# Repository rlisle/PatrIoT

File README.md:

# Patriot
Patriot is an open source, hobby IoT project using 
Particle.io Photon 2 devices, and optionally Siri, HomeKit, MQTT, and/or iOS apps.

It is intended to help other hobbyists quickly create Internet-of-Things
projects that can be controlled using Voice (Siri) and iOS devices
without having to recreate new HomeKit programming or iOS apps.

This project consists of published particle.io Photon 2
libraries (IoTlib and plugins).

Note that previously a published Alexa Smart Home skill (Patriot) was used.
The use of Alexa has been replaced with Siri and HomeKit. 
I apologize to those that want Alexa support, but it was getting to be too much work for me to support both iOS and Alexa by myself in my spare time.

The HomeKit "Home" app can be used with your old iPhones
to provide a touch display control panel.

Your Photon 2 based IoT projects can be created using any of the 
standard particle.io development tools (Web IDE,
Particle IDE, or Particle CLI).

The main objective is to allow the creation of networks of IoT
devices that can communicate with each other, and is:
1. Easily extensible: new devices can be added without having to modify existing devices.
2. Super simple to program
3. Reuses existing code, including the HomeKit apps, iOS apps, and Photon library code.

Refer to the older article [Alexa Controlled Photon Project without Alexa Coding](https://www.hackster.io/patriot-iot/alexa-controlled-photon-project-without-alexa-coding-f47d84)
on Hackster.io or my blog at lisles.net for some historical information.

## Devices
Particle.io Photon 2's are used due to their ease of use and great
support. I had originally created my own low cost printed circuit boards (PCBs), but since then ControlEverything (NCD.io) has released a series of Photon based boards that make it even easier to use.

These have wireless built-in, and can be programmed
over-the-air (OTA) so all they need is power to get started.

I've provided a set of source code files and instructions
that can be used to simplify
programming IoT devices using Particle's $19 Photon 2.

I've still publish the Eagle files and instructions for creating
general purpose IoT printed circuit boards.
PCBs can be ordered from China for about $1.50 each.
However, I've found that purchasing boards from NCD.io is quicker and the boards are much higher quality. The prices are very reasonable. For example, a simple Photon board with a power supply that works directly with my RV's 12v power and has screw terminals for connecting to the Photon's pins is only $15.

## Homebridge
HomeKit support is provided by Homebridge and the MQTTThingy plugin.

This allows Siri to control Patriot devices using your iPhone, Homepod, or Apple TV.

## Release History
Refer to the (Releases page)[https://github.com/rlisle/Patriot/releases]
for release history.

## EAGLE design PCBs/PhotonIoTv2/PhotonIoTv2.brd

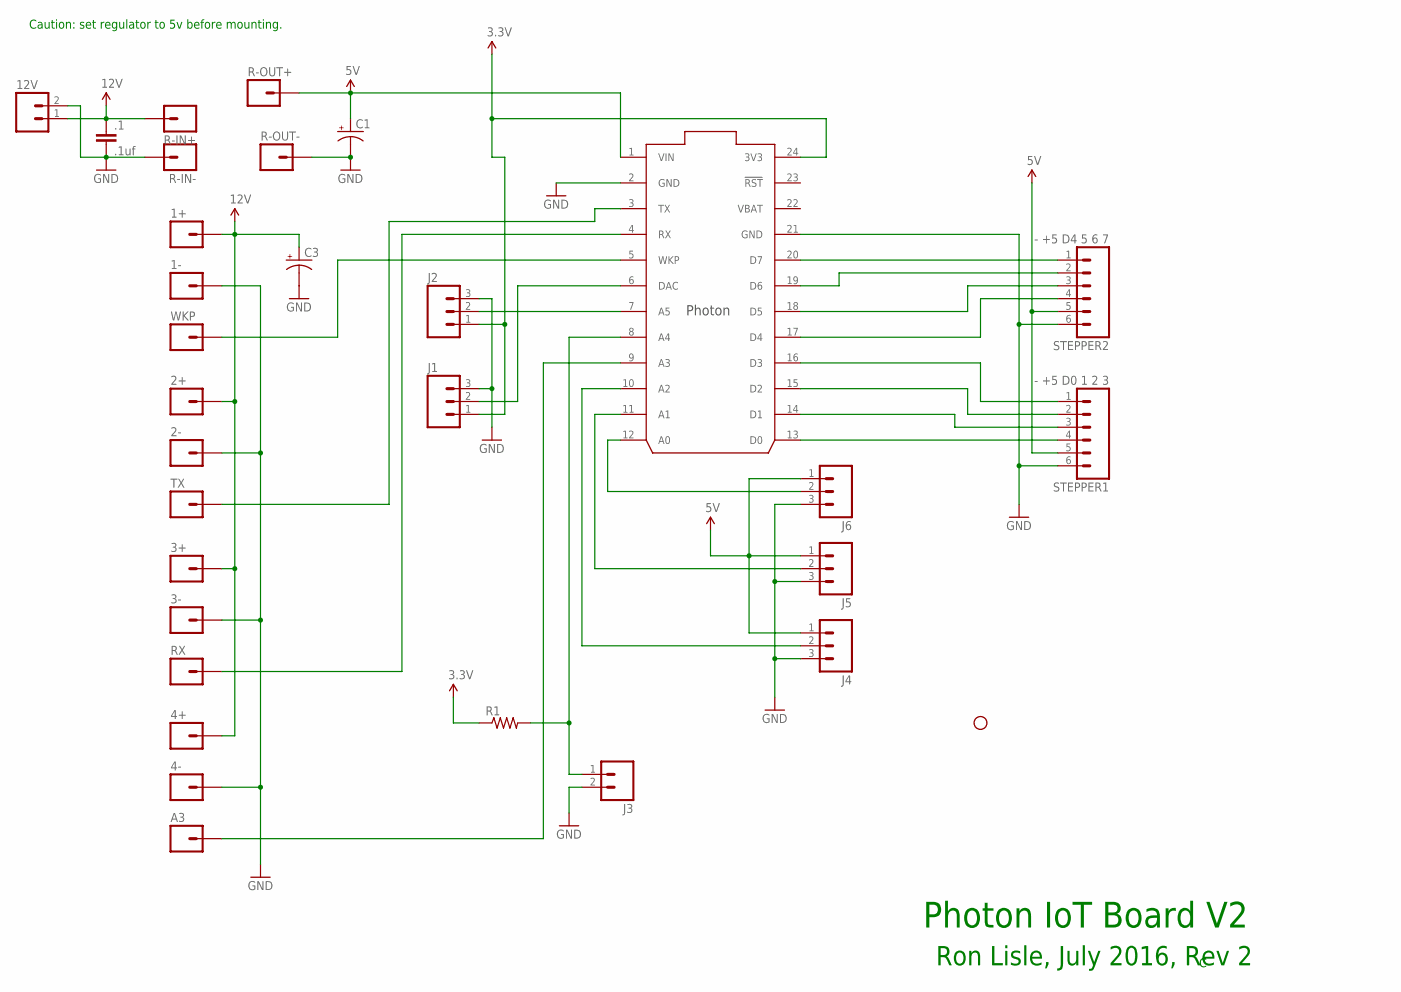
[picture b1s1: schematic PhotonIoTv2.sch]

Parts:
1+, 1-, 2+, 2-, 3+, 3-, 4+, 4-: M01PTH; 1X01
12V: M025MM; SCREWTERMINAL-5MM-2
.1: .1uf; CAP-PTH-SMALL-KIT
A3: M01PTH; 1X01
C1, C3: 10UF-25V-20%(PTH)KIT; CPOL-RADIAL-10UF-25V-KIT
J1, J2, J4, J5, J6: M03PTH; 1X03
J3: M02PTH; 1X02
R1: R-US_0204/7; 0204/7
R-IN+: M01PTH; 1X01
R-IN-: M01PTH; 1X01
R-OUT+: M01PTH; 1X01
R-OUT-: M01PTH; 1X01
RX: M01PTH; 1X01
STANDOFF1: STAND-OFF
STEPPER1: - +5 D0 1 2 3; 1X06_LOCK_LONGPADS
STEPPER2: - +5 D4 5 6 7; 1X06_LOCK_LONGPADS
TX: M01PTH; 1X01
U$1: Photon with headers; PHOTON
WKP: M01PTH; 1X01

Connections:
3.3V: J1.1, J2.1, R1.1, U$1.24 (3V3)
5V: C1.1 (+), J4.1, J5.1, J6.1, R-OUT+.1, STEPPER1.5, STEPPER2.5, U$1.1 (VIN)
12V: 1+.1, 2+.1, 3+.1, 4+.1, 12V.1, .1.1, C3.1 (+), R-IN+.1
GND: 1-.1, 2-.1, 3-.1, 4-.1, 12V.2, .1.2, C1.2 (-), C3.2 (-), J1.3, J2.3, J3.2, J4.3, J5.3, J6.3, R-IN-.1, R-OUT-.1, STEPPER1.6, STEPPER2.6, U$1.2 (GND), U$1.21 (GND)
unnamed: STEPPER1.2, U$1.15 (D2)
unnamed: STEPPER2.1, U$1.20 (D7)
unnamed: STEPPER2.3, U$1.18 (D5)
unnamed: STEPPER2.4, U$1.17 (D4)
unnamed: STEPPER1.1, U$1.16 (D3)
unnamed: A3.1, U$1.9 (A3)
unnamed: J4.2, U$1.10 (A2)
unnamed: STEPPER1.3, U$1.14 (D1)
unnamed: STEPPER1.4, U$1.13 (D0)
unnamed: U$1.5 (WKP), WKP.1
unnamed: J3.1, R1.2, U$1.8 (A4)
unnamed: J2.2, U$1.7 (A5)
unnamed: STEPPER2.2, U$1.19 (D6)
unnamed: J5.2, U$1.11 (A1)
unnamed: J6.2, U$1.12 (A0)
unnamed: J1.2, U$1.6 (DAC)
unnamed: TX.1, U$1.3 (TX)
unnamed: RX.1, U$1.4 (RX)
VBAT: U$1.22 (VBAT)

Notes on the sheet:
Ron Lisle, July 2016, Rev 2
Photon IoT Board V2
Caution: set regulator to 5v before mounting.

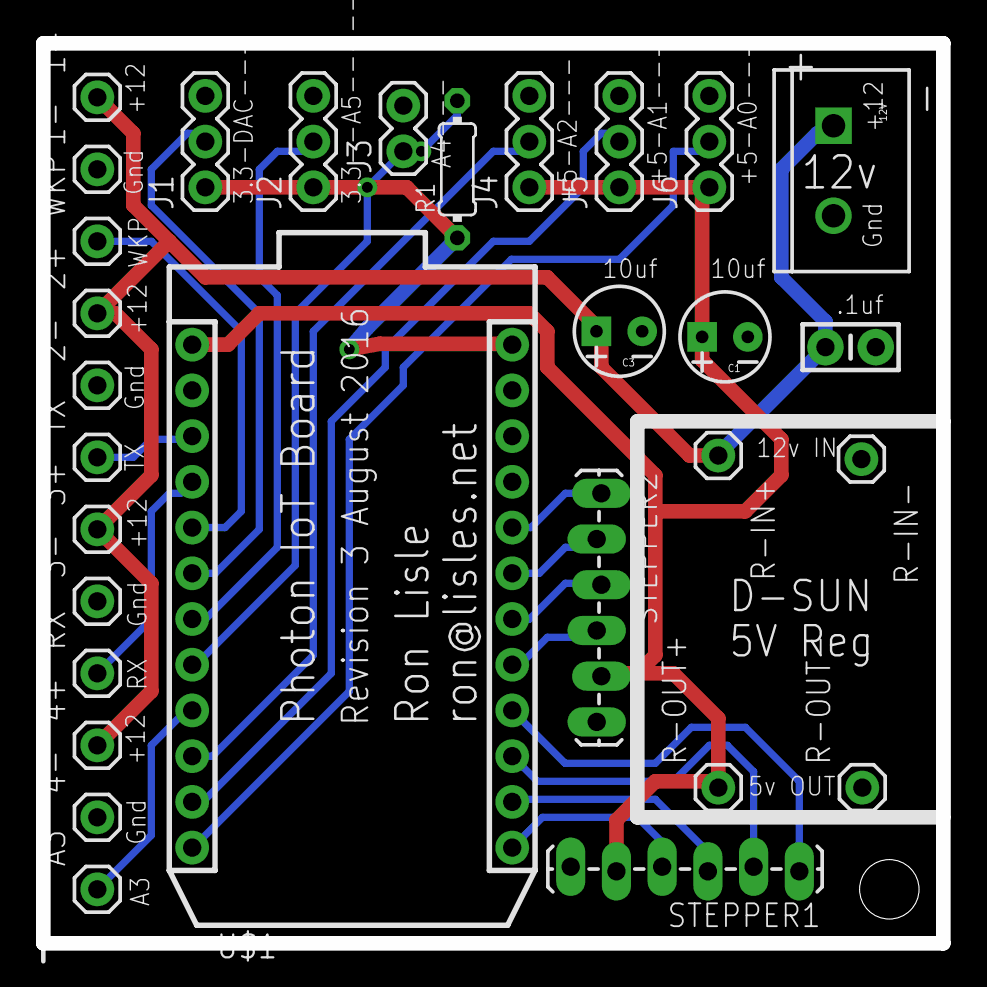
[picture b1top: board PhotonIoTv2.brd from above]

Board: 2 copper layers, 50.0 x 50.0 mm, 31 parts (0 on the bottom side), 22 nets.

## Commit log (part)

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2022-11-13 Latlong (#150)
    * wip
    * wip
2022-11-22 Timeout2 (#151)
    * wip
    * wip
    * wip
    * wip
    * wip
    * wip
2022-11-25 Revert to AUTOMATIC (#152)
    * wip
    * wip
    * wip
    * wip
    * wip
    * wip
2022-11-26 Retry MQTT if disconnected
2022-11-26 Move MQTT into project
2022-11-26 addDevice() update status
2022-11-26 Move MQTT into project (#153)
    * Retry MQTT if disconnected
    * Move MQTT into project
    * wip
    * wip
    * addDevice() update status
2022-12-01 Separate log topic
2022-12-04 MQTT QoS 1 (#154)
    * wip
    * wip
    * wip
    * wip
    * Separate log topic
    * wip
2022-12-07 Fix Curtain plugin (#155)
    * wip
    * wip
    * wip
    * wip
    * wip
    * wip
2022-12-07 Bump minimatch and mocha in /Xcode (#149)
    Bumps [minimatch](https://github.com/isaacs/minimatch) to 5.0.1 and updates ancestor dependency [mocha](https://github.com/mochajs/mocha). These dependencies need to be updated together.
    Updates `minimatch` from 3.0.4 to 5.0.1
    - [Release notes](https://github.com/isaacs/minimatch/releases)
    - [Commits](https://github.com/isaacs/minimatch/compare/v3.0.4...v5.0.1)
    Updates `mocha` from 8.2.1 to 10.1.0
    - [Release notes](https://github.com/mochajs/mocha/releases)
2022-12-07 Bump qs from 6.9.6 to 6.11.0 in /Xcode
    Bumps [qs](https://github.com/ljharb/qs) from 6.9.6 to 6.11.0.
    - [Release notes](https://github.com/ljharb/qs/releases)
    - [Changelog](https://github.com/ljharb/qs/blob/main/CHANGELOG.md)
    - [Commits](https://github.com/ljharb/qs/compare/v6.9.6...v6.11.0)
    ---
    updated-dependencies:
2022-12-07 Bump qs from 6.9.6 to 6.11.0 in /Xcode (#156)
    Bumps [qs](https://github.com/ljharb/qs) from 6.9.6 to 6.11.0.
    - [Release notes](https://github.com/ljharb/qs/releases)
    - [Changelog](https://github.com/ljharb/qs/blob/main/CHANGELOG.md)
    - [Commits](https://github.com/ljharb/qs/compare/v6.9.6...v6.11.0)
    ---
    updated-dependencies:
2022-12-12 Create voltage plugin
2022-12-14 Switches and Voltage (#157)
    * wip
    * wip
    * wip
    * wip
    * wip
    * wip
2022-12-30 ShellyPower
2023-01-01 Power Monitor (#158)
    * wip
    * wip
    * wip
    * wip
    * wip
    * wip
2023-01-24 Bump cookiejar from 2.1.2 to 2.1.4 in /Xcode
    Bumps [cookiejar](https://github.com/bmeck/node-cookiejar) from 2.1.2 to 2.1.4.
    - [Release notes](https://github.com/bmeck/node-cookiejar/releases)
    - [Commits](https://github.com/bmeck/node-cookiejar/commits)
    ---
    updated-dependencies:
    - dependency-name: cookiejar
2023-04-10 Bump xml2js and aws-sdk in /Xcode
    Bumps [xml2js](https://github.com/Leonidas-from-XIV/node-xml2js) and [aws-sdk](https://github.com/aws/aws-sdk-js). These dependencies needed to be updated together.
    Updates `xml2js` from 0.4.19 to 0.5.0
    - [Release notes](https://github.com/Leonidas-from-XIV/node-xml2js/releases)
    - [Commits](https://github.com/Leonidas-from-XIV/node-xml2js/compare/0.4.19...0.5.0)
    Updates `aws-sdk` from 2.833.0 to 2.1354.0
    - [Release notes](https://github.com/aws/aws-sdk-js/releases)
2023-05-27 v9.1.0
2023-05-28 Add Awning plugin
2023-06-06 Switch to AUTOMATIC
2023-06-21 Add MQTT test
2023-06-24 outOfMemory
2023-06-24 cleanup
2023-06-24 Threads (#161)
    * v9.1.0
    * wip
    * Add Awning plugin
    * wip
    * wip
    * wip
2023-07-05 restore normal timing
2023-07-07 Increase alive to 15 mins
2023-07-24 Restart (#162)
    * wip
    * wip
    * wip
    * wip
    * cleanup
    * restore normal timing
2023-08-18 embed NCD8Light
2023-08-18 Embed curtain
2023-08-19 Combine pca9634 init
2023-08-20 Code folding
2023-08-23 left_slide2
2023-08-24 group devices
2023-08-26 Rename NCD16Light
2023-08-26 pca9685 .h
2023-08-26 pca9685.cpp
2023-08-26 stable fp
2023-08-26 def static address - stable
2023-08-26 Use PCA9685
2023-08-27 refactor light - stable
2023-08-27 Fix FP address
2023-08-27 MCP23008
2023-08-29 Update switch logic
2023-08-30 Disable all devices for debug
2023-09-01 Fix FP NCD16Light
2023-09-02 Fix status
2023-09-02 devices calculatedVariable
2023-09-02 checklist computed variable
2023-09-09 Adjust dimming curve
2023-09-09 Measure timing loop
2023-09-10 Convert NCD8Light
2023-09-10 Fix pca9634
2023-09-11 use mcp23008 for curtain and 4switch
2023-09-13 Cache input
2023-09-17 Update NCD8Light comments
2023-09-17 FP ncd8light
2023-09-20 Fix dim to 0
2023-09-24 Fix curve
2023-09-24 Handle 99.5
2023-09-25 Fix duration int8_t
2023-09-27 Update leftslide2
2023-09-30 Add fuse info
2023-10-13 Curve (#163)
    * wip
    * wip
    * wip
    * wip
    * wip
    * wip
2023-10-13 Update readme for photon 2
2023-10-13 Curve2 (#164)
    * Adjust dimming curve
    * Cleanup
    * Measure timing loop
    * Cleanup
    * Convert NCD8Light
    * wip
2023-10-13 Convert FP to 16x
2023-10-14 NCD16 pins
2023-10-16 Adjust dimmer assignments
2023-10-16 Dimmer16 (#165)
    * Adjust dimming curve
    * Cleanup
    * Measure timing loop
    * Cleanup
    * Convert NCD8Light
    * wip
2023-11-17 Add setSSID
2023-11-27 Set ssid (#166)
    * wip
    * Add setSSID
    * wip
    * wip
    * wip
2023-11-28 Set ssid additional changes (#168)
    * wip
    * Add setSSID
    * wip
    * wip
    * wip
2024-01-15 Ignore secrets.h
2024-01-15 vscode
2024-01-16 msecs typedef
2024-01-16 create BedBath test controller
2024-01-29 Photon2b (#169)
    * create BedBath test controller
    * Delete binary files
2024-02-04 changeHandler
2024-02-05 Remove separate ...2 dirs
2024-02-08 Add behaviors
2024-02-11 Actions (#170)
    * create BedBath test controller
    * Delete binary files
    * changeHandler
    * wip
    * wip
    * wip
2024-02-13 Change alive to 60 mins
2024-02-13 Fix door light
2024-02-17 Moving status to Device
2024-02-19 Motion (#171)
    * wip
    * wip
    * wip
    * wip
    * wip
    * wip
2024-02-19 Move shortcuts to IoT
2024-03-28 Fix nook
2024-03-29 copy of Zigbee2MQTT config
2024-03-29 Add OfficeValence
2024-04-06 Config for new Sonoff -p adapter
2024-04-18 Remove 2 from FrontPanel2
2024-04-23 Bump formidable and particle-api-js in /Xcode
    Removes [formidable](https://github.com/node-formidable/formidable). It's no longer used after updating ancestor dependency [particle-api-js](https://github.com/particle-iot/particle-api-js). These d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
    Removes `formidable`
    Updates `particle-api-js` from 8.0.0 to 10.4.3
    - [Release notes](https://github.com/particle-iot/particle-api-js/releases)
    - [Changelog](https://github.com/particle-iot/particle-api-js/blob/master/CHANGELOG.md)
    - [Commits](https://github.com/particle-iot/particle-api-js/compare/v8.0.0...v10.4.3)
2024-04-25 Update FrontPanel
2024-04-25 Cleanup LeftSlide
2024-04-25 Update RearPanel
2024-05-16 Update for RPi
2024-05-18 Change plantlight to ZigbeeOutlet
2024-06-16 Bump braces from 3.0.2 to 3.0.3 in /Xcode
    Bumps [braces](https://github.com/micromatch/braces) from 3.0.2 to 3.0.3.
    - [Changelog](https://github.com/micromatch/braces/blob/master/CHANGELOG.md)
    - [Commits](https://github.com/micromatch/braces/compare/3.0.2...3.0.3)
    ---
    updated-dependencies:
    - dependency-name: braces
